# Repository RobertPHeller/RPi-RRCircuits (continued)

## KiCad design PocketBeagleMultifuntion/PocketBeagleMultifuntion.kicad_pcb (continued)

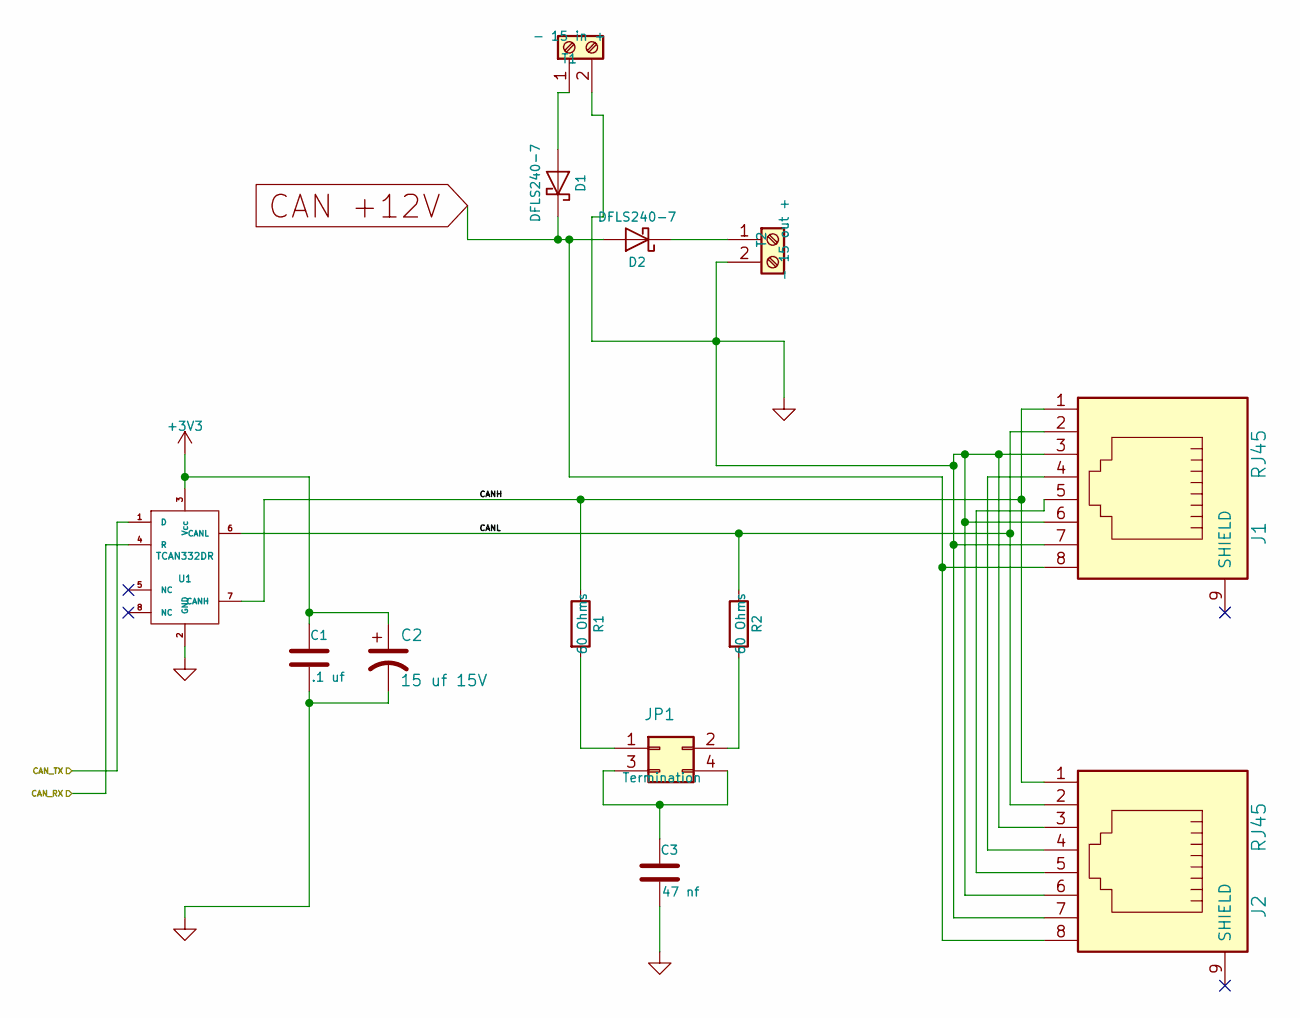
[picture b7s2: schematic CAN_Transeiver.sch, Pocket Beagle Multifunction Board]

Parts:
C1: .1 uf; C_0603; Mouser Part Number 710-885012206095
C2: 15 uf 15V; CP_Elec_4x5.7; Mouser Part Number 647-UUD1C150MCL
C3: 47 nf; C_0603; Mouser Part Number 710-885012206093
D1, D2: DFLS240-7; D_SMB; Mouser Part Number 621-DFLS240-7
J1, J2: RJ45; RJ45_8N-S; Mouser Part Number 710-615008144221
JP1: Termination; Pin_Header_Straight_2x02_Pitch2.54mm; Mouser Part Number 649-67997-404HLF
R1, R2: 60 Ohms; R_1206; Mouser Part Number 71-CRCW120660R0KNAIF
T1: - 15 in +; TerminalBlock_Pheonix_MPT-2.54mm_2pol; Mouser Part Number 651-1725656
T2: - 15 out +; TerminalBlock_Pheonix_MPT-2.54mm_2pol; Mouser Part Number 651-1725656
U1: TCAN332DR; SOIC-8_3.9x4.9mm_Pitch1.27mm; Mouser Part Number 595-TCAN332DR

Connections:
+3V3: C1.1, C2.1, U1.3 (Vcc); also elsewhere on the board
/CAN1_RX: U1.4 (R); also elsewhere on the board
/CAN1_TX: U1.1 (D); also elsewhere on the board
/CAN Transceiver/CANH: J1.1, J2.1, R1.1, U1.7 (CANH)
/CAN Transceiver/CANL: J1.2, J2.2, R2.1, U1.6 (CANL)
CAN +12V: D1.1 (K), D2.2 (A), J1.8, J2.8; also elsewhere on the board
GND: C1.2, C2.2, C3.2, J1.3, J1.6, J1.7, J2.3, J2.6, J2.7, T1.2, T2.2, U1.2 (GND); also elsewhere on the board
unnamed: C3.1, JP1.3, JP1.4
unnamed: D1.2 (A), T1.1
unnamed: D2.1 (K), T2.1
unnamed: J1.4, J2.4
unnamed: J1.5, J2.5
unnamed: JP1.1, R1.2
unnamed: JP1.2, R2.2

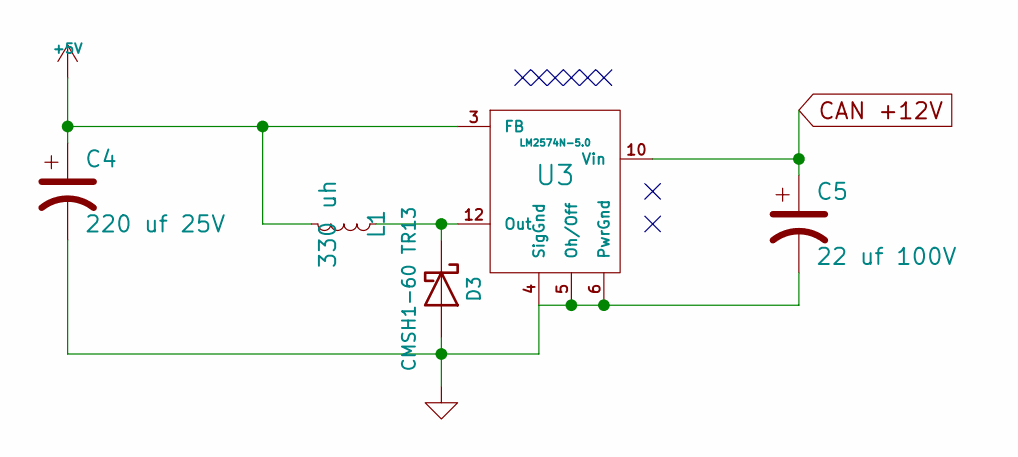
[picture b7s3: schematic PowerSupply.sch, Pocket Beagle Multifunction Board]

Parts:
C4: 220 uf 25V; CP_Elec_8x10; Mouser Part Number 647-UWT1E221MNL1GS
C5: 22 uf 100V; CP_Elec_8x10; Mouser Part Number 647-UUX2A220MNL6GS
D3: CMSH1-60 TR13; D_SMB; Mouser Part Number 610-CMSH1-60TR13
L1: 330 uh; SRN1060; Mouser Part Number 652-SRN1060-331M
U3: LM2574N-5.0; SOIC-14_7.4x8.7mm_Pitch1.27mm; Mouser Part Number 926-LM2574N-5.0/NOPB

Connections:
+5V: C4.1, L1.2, U3.3 (FB); also elsewhere on the board
CAN +12V: C5.1, U3.10 (Vin); also elsewhere on the board
GND: C4.2, C5.2, D3.2 (A), U3.4 (SigGnd), U3.5 (Oh/Off), U3.6 (PwrGnd); also elsewhere on the board
unnamed: D3.1 (K), L1.1, U3.12 (Out)

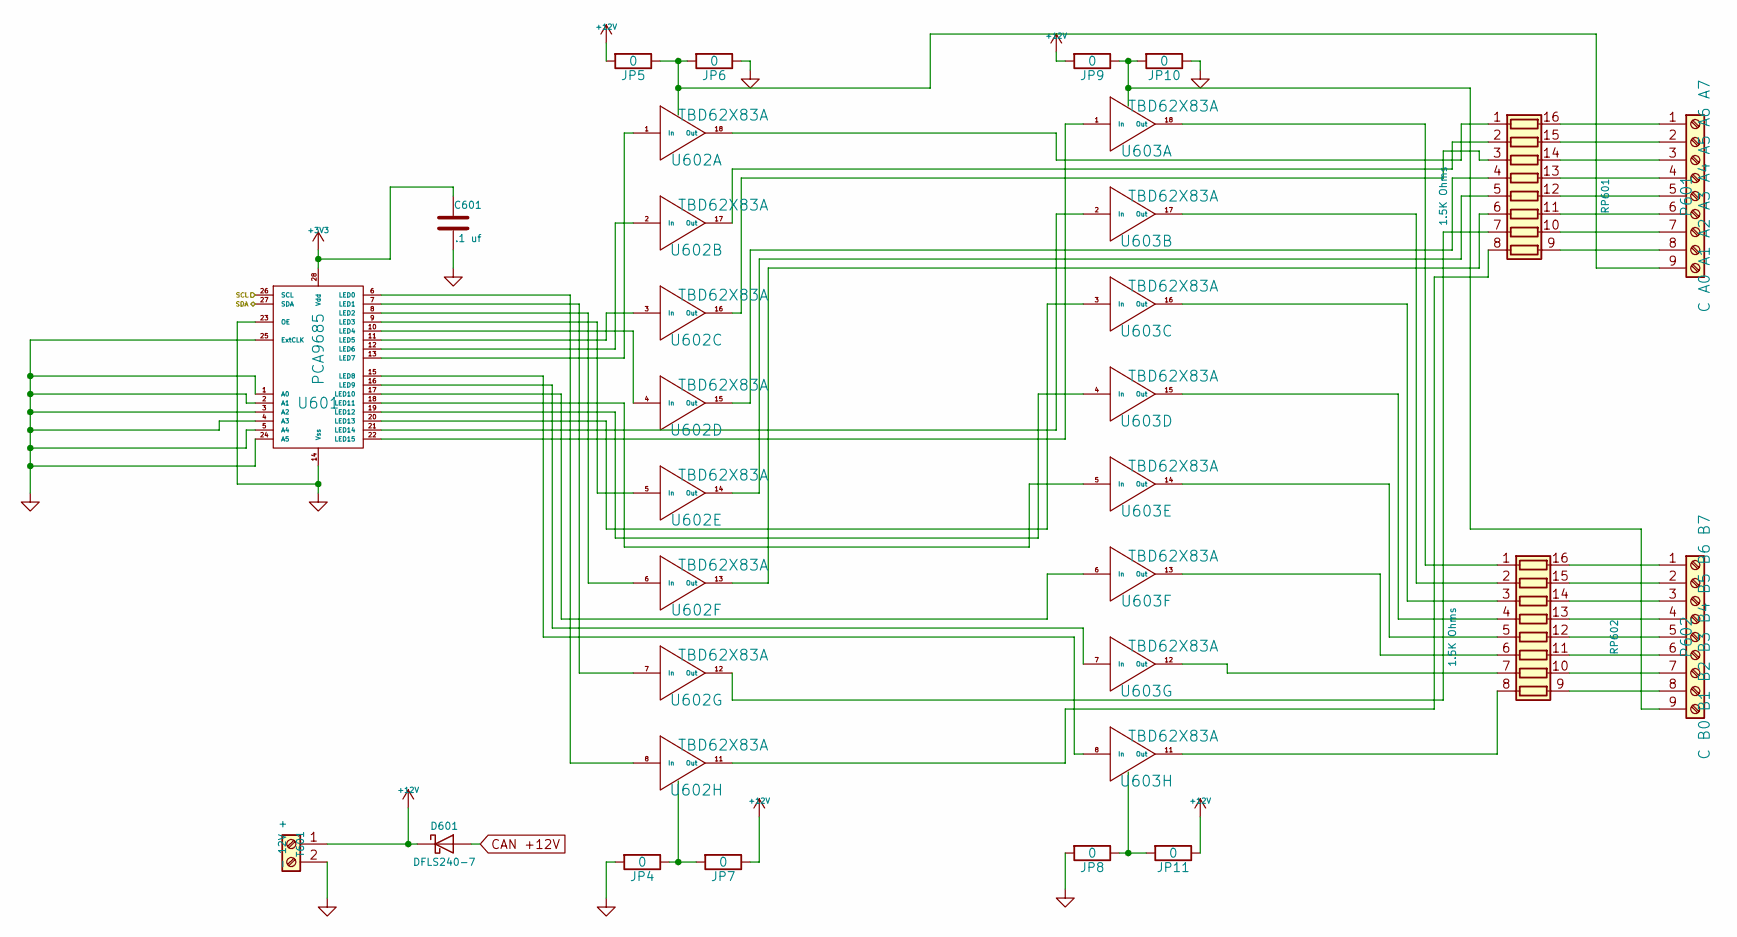
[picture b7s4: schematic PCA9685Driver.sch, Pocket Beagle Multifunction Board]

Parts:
C601: .1 uf; C_0603; Mouser Part Number 710-885012206095
D601: DFLS240-7; D_SMB; Mouser Part Number 621-DFLS240-7
JP4, JP5, JP6, JP7, JP8, JP9, JP10, JP11: 0; R_1206; Mouser Part Number 71-CRCW12060000Z0EBC
P601: C A0 A1 A2 A3 A4 A5 A6 A7; TerminalBlock_Pheonix_MPT-2.54mm_9pol; Mouser Part Number 651-1725724
P602: C B0 B1 B2 B3 B4 B5 B6 B7; TerminalBlock_Pheonix_MPT-2.54mm_9pol; Mouser Part Number 651-1725724
RP601, RP602: 1.5K Ohms; 4816P; Mouser Part Number 652-4816P-T1LF-1.5K
T601: - 12V +; TerminalBlock_Pheonix_MPT-2.54mm_2pol; Mouser Part Number 651-1725656
U601: PCA9685; TSSOP-28_4.4x9.7mm_Pitch0.65mm; Mouser Part Number 771-PCA9685PW,118
U602, U603: TBD62X83A; SOIC-18W_7.5x11.6mm_Pitch1.27mm; Mouser Part Number 757-TBD62083AFG or 757-TBD62783AFG

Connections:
+3V3: C601.1, U601.28 (Vdd); also elsewhere on the board
+12V: D601.1 (K), JP5.2, JP7.1, JP9.2, JP11.1, T601.1; also elsewhere on the board
/SCL: U601.26 (SCL); also elsewhere on the board
/SDA: U601.27 (SDA); also elsewhere on the board
CAN +12V: D601.2 (A); also elsewhere on the board
GND: C601.2, JP4.2, JP6.1, JP8.2, JP10.1, T601.2, U601.1 (A0), U601.2 (A1), U601.3 (A2), U601.4 (A3), U601.5 (A4), U601.14 (Vss), U601.23 (OE), U601.24 (A5), U601.25 (ExtCLK); also elsewhere on the board
unnamed: JP4.1, JP7.2, U602.9 (IC)
unnamed: JP5.1, JP6.2, P601.9, U602.10 (OC)
unnamed: JP9.1, JP10.2, P602.9, U603.10 (OC)
unnamed: JP8.1, JP11.2, U603.9 (IC)
unnamed: P601.1, RP601.16 (R1.2)
unnamed: P601.2, RP601.15 (R2.2)
unnamed: P601.3, RP601.14 (R3.2)
unnamed: P601.4, RP601.13 (R4.2)
unnamed: P601.5, RP601.12 (R5.2)
unnamed: P601.6, RP601.11 (R6.2)
unnamed: P601.7, RP601.10 (R7.2)
unnamed: P601.8, RP601.9 (R8.2)
unnamed: P602.1, RP602.16 (R1.2)
unnamed: P602.2, RP602.15 (R2.2)
unnamed: P602.3, RP602.14 (R3.2)
unnamed: P602.4, RP602.13 (R4.2)
unnamed: P602.5, RP602.12 (R5.2)
unnamed: P602.6, RP602.11 (R6.2)
unnamed: P602.7, RP602.10 (R7.2)
unnamed: P602.8, RP602.9 (R8.2)
unnamed: RP601.1 (R1.1), U602.18 (Out)
unnamed: RP601.2 (R2.1), U602.17 (Out)
unnamed: RP601.3 (R3.1), U602.16 (Out)
unnamed: RP601.4 (R4.1), U602.15 (Out)
unnamed: RP601.5 (R5.1), U602.14 (Out)
unnamed: RP601.6 (R6.1), U602.13 (Out)
unnamed: RP601.7 (R7.1), U602.12 (Out)
unnamed: RP601.8 (R8.1), U602.11 (Out)
unnamed: RP602.1 (R1.1), U603.18 (Out)
unnamed: RP602.2 (R2.1), U603.17 (Out)
unnamed: RP602.3 (R3.1), U603.16 (Out)
unnamed: RP602.4 (R4.1), U603.15 (Out)
unnamed: RP602.5 (R5.1), U603.14 (Out)
unnamed: RP602.6 (R6.1), U603.13 (Out)
unnamed: RP602.7 (R7.1), U603.12 (Out)
unnamed: RP602.8 (R8.1), U603.11 (Out)
unnamed: U601.6 (LED0), U602.8 (In)
unnamed: U601.7 (LED1), U602.7 (In)
unnamed: U601.8 (LED2), U602.6 (In)
unnamed: U601.9 (LED3), U602.5 (In)
unnamed: U601.10 (LED4), U602.4 (In)
unnamed: U601.11 (LED5), U602.3 (In)
unnamed: U601.12 (LED6), U602.2 (In)
unnamed: U601.13 (LED7), U602.1 (In)
unnamed: U601.15 (LED8), U603.8 (In)
unnamed: U601.16 (LED9), U603.7 (In)
unnamed: U601.17 (LED10), U603.6 (In)
unnamed: U601.18 (LED11), U603.5 (In)
unnamed: U601.19 (LED12), U603.4 (In)
unnamed: U601.20 (LED13), U603.3 (In)
unnamed: U601.21 (LED14), U603.2 (In)
unnamed: U601.22 (LED15), U603.1 (In)

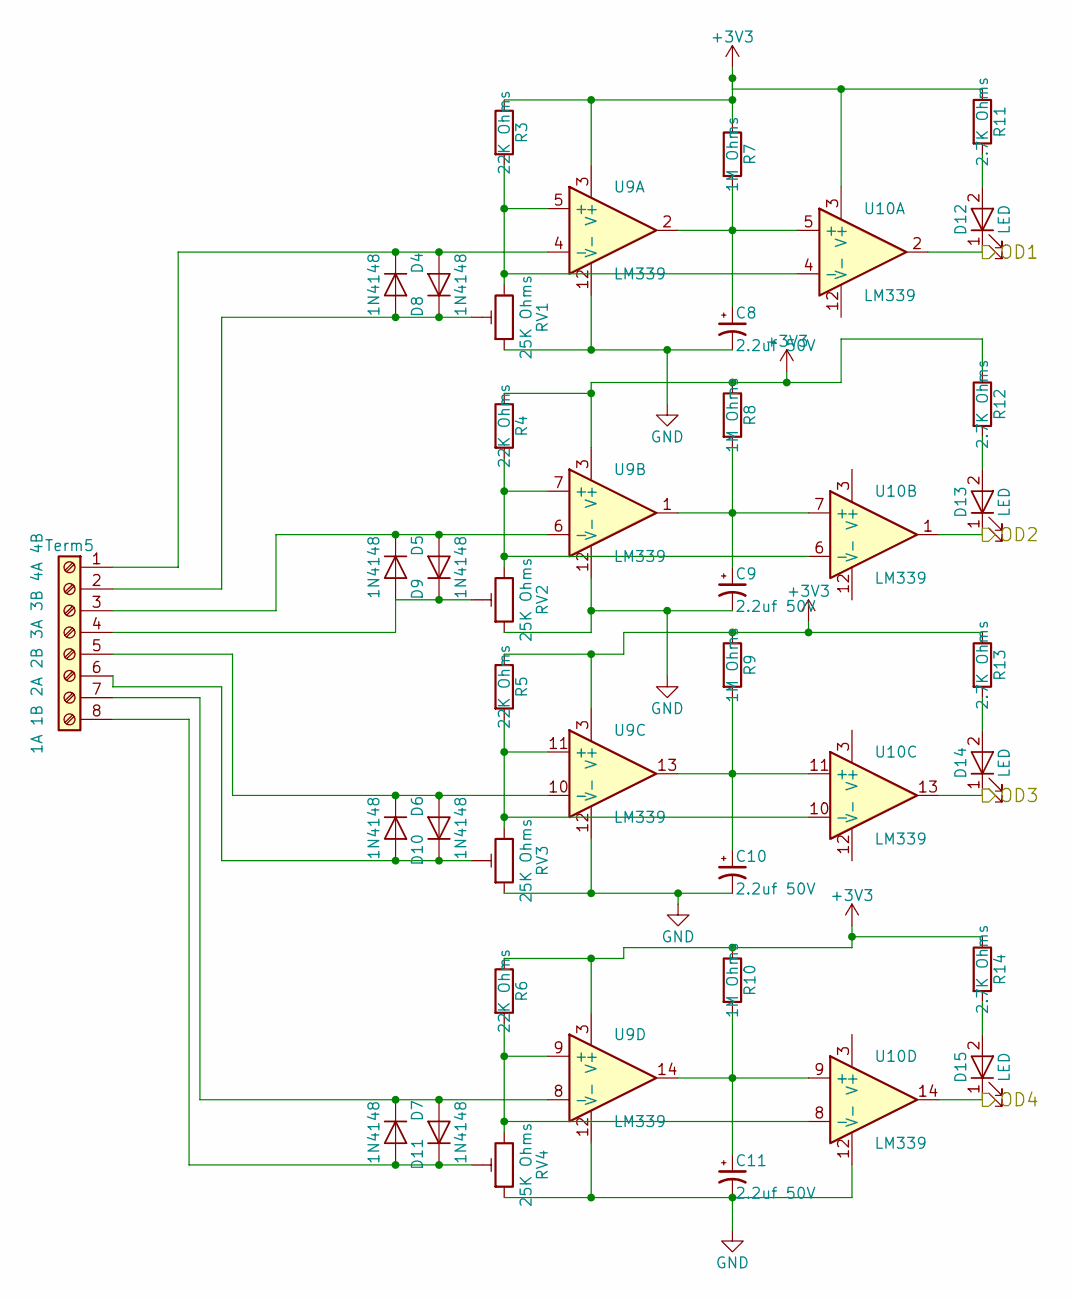
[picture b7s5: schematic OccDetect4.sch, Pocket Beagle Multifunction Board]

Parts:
C8, C9, C10, C11: 2.2uf 50V; CP_Elec_4x5.7; Mouser Part Number 710-865080140002
D4, D5, D6, D7, D8, D9, D10, D11: 1N4148; D_SOD-123; Mouser Part Number 750-1N4148WS-HF
D12, D13, D14, D15: LED; LED_0603; Mouser Part Number 710-150060SS55040
R3, R4, R5, R6: 22K Ohms; R_0603; Mouser Part Number 71-RCG060322K0JNEA
R7, R8, R9, R10: 1M Ohms; R_0603; Mouser Part Number 71-CRCW06031M00JNEAC
R11, R12, R13, R14: 2.7K Ohms; R_0603; Mouser Part Number 71-CRCW06032K70JNEAC
RV1, RV2, RV3, RV4: 25K Ohms; Potentiometer_Trimmer_Bourns_3214J; Mouser Part Number 652-3314J-1-253E
Term5: 1A 1B 2A 2B 3A 3B 4A 4B; TerminalBlock_Pheonix_MPT-2.54mm_8pol; Mouser Part Number 651-1725711
U9, U10: LM339; SOIC-14_3.9x8.7mm_Pitch1.27mm

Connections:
+3V3: R3.1, R4.1, R5.1, R6.1, R7.1, R8.1, R9.1, R10.1, R11.1, R12.1, R13.1, R14.1, U9.3 (V+), U10.3 (V+); also elsewhere on the board
/GPIO7: D12.1 (K), U10.2; also elsewhere on the board
/GPIO19: D13.1 (K), U10.1; also elsewhere on the board
/GPIO20: D14.1 (K), U10.13; also elsewhere on the board
/GPIO23: D15.1 (K), U10.14; also elsewhere on the board
GND: C8.2, C9.2, C10.2, C11.2, RV1.1, RV2.1, RV3.1, RV4.1, U9.12 (V-), U10.12 (V-); also elsewhere on the board
unnamed: C8.1, R7.2, U9.2, U10.5 (+)
unnamed: C9.1, R8.2, U9.1, U10.7 (+)
unnamed: C10.1, R9.2, U9.13, U10.11 (+)
unnamed: C11.1, R10.2, U9.14, U10.9 (+)
unnamed: D4.1 (K), D8.2 (A), Term5.1, U9.4 (-)
unnamed: D4.2 (A), D8.1 (K), RV1.2, Term5.2
unnamed: D5.1 (K), D9.2 (A), Term5.3, U9.6 (-)
unnamed: D5.2 (A), D9.1 (K), RV2.2, Term5.4
unnamed: D6.2 (A), D10.1 (K), RV3.2, Term5.6
unnamed: D6.1 (K), D10.2 (A), Term5.5, U9.10 (-)
unnamed: D7.2 (A), D11.1 (K), RV4.2, Term5.8
unnamed: D7.1 (K), D11.2 (A), Term5.7, U9.8 (-)
unnamed: D12.2 (A), R11.2
unnamed: D13.2 (A), R12.2
unnamed: D14.2 (A), R13.2
unnamed: D15.2 (A), R14.2
unnamed: R3.2, RV1.3, U9.5 (+), U10.4 (-)
unnamed: R4.2, RV2.3, U9.7 (+), U10.6 (-)
unnamed: R5.2, RV3.3, U9.11 (+), U10.10 (-)
unnamed: R6.2, RV4.3, U9.9 (+), U10.8 (-)

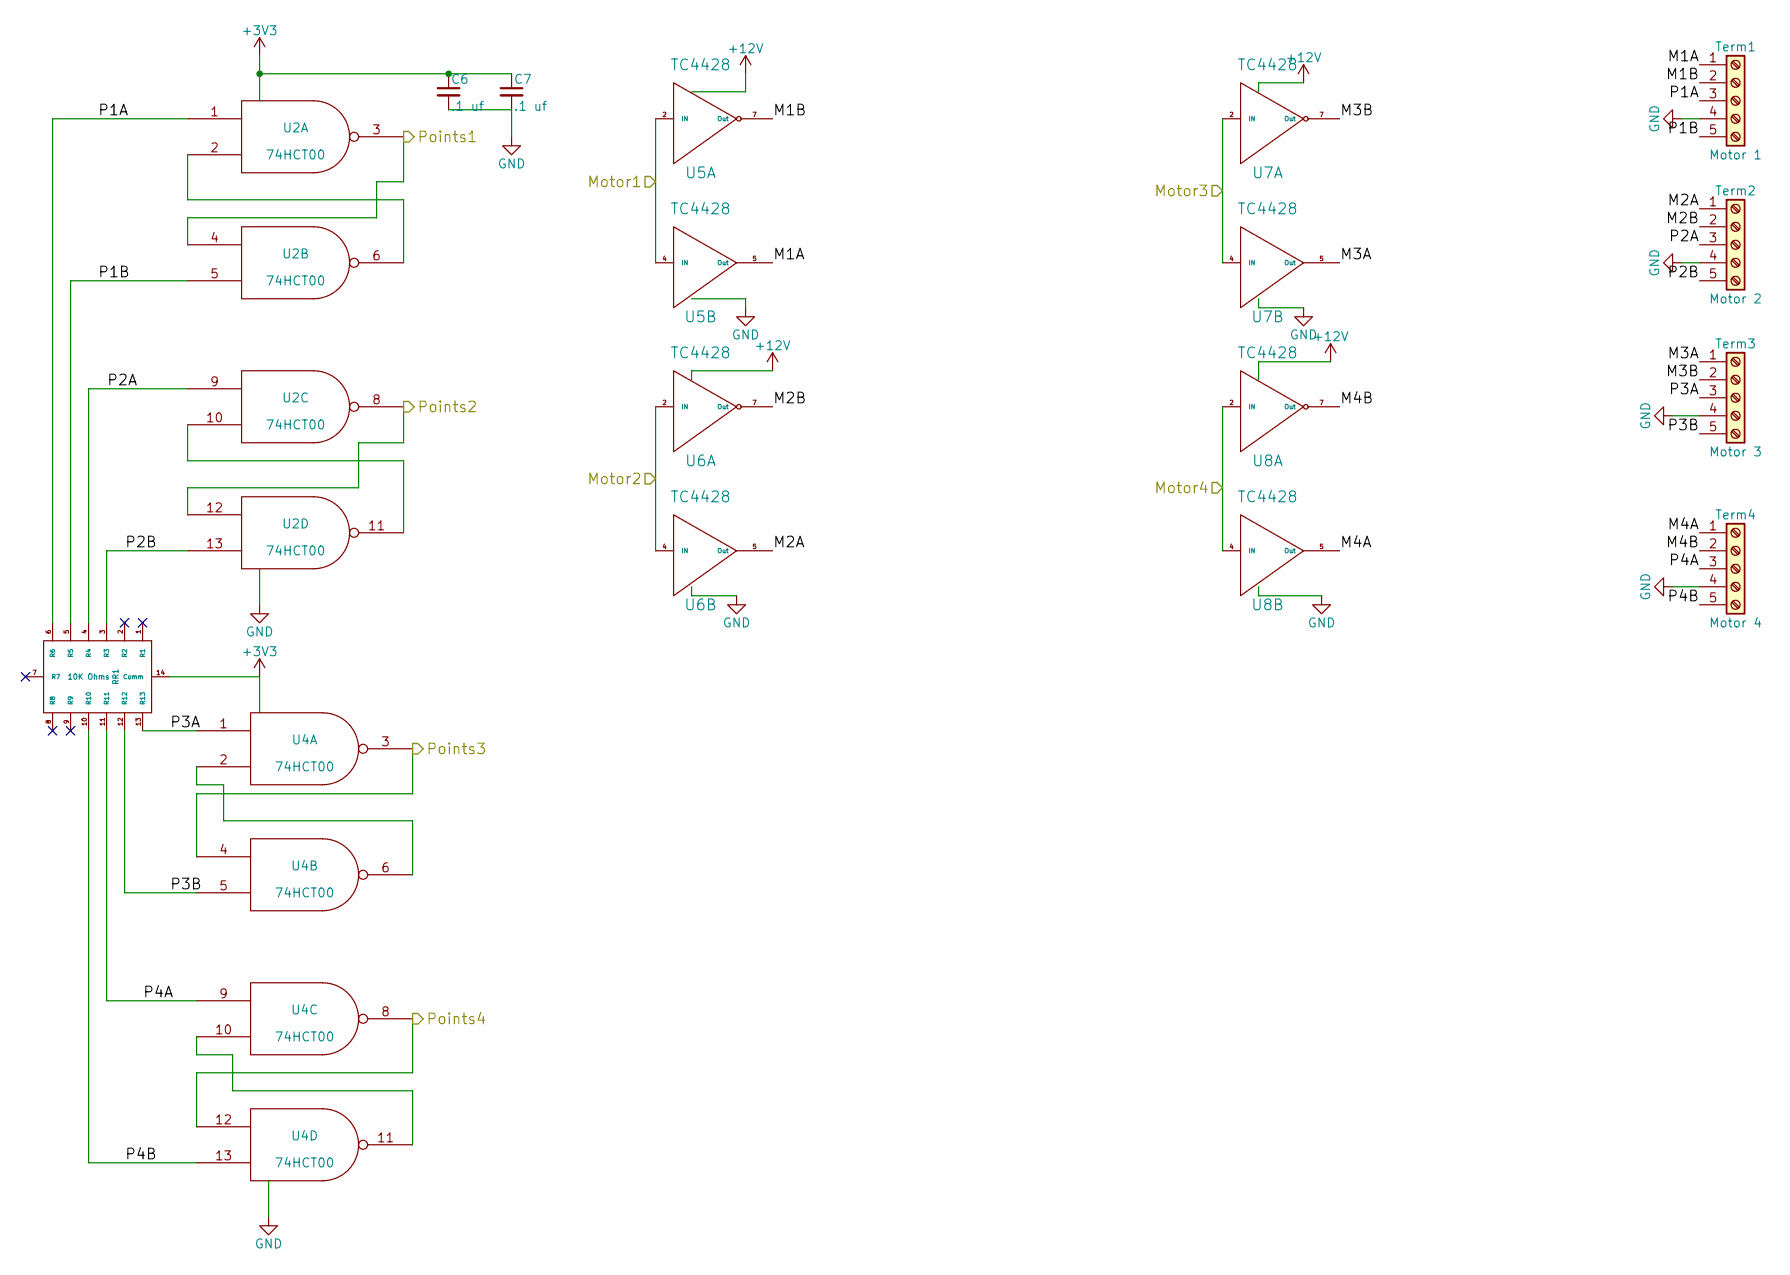
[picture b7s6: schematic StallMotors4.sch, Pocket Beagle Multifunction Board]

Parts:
C6, C7: .1 uf; C_0603; Mouser Part Number 710-885012206095
RR1: 10K Ohms; 4814P; Mouser Part Number 652-4814P-2LF-10K
Term1: Motor 1; TerminalBlock_Pheonix_MPT-2.54mm_5pol; Mouser Part Number 651-1725685
Term2: Motor 2; TerminalBlock_Pheonix_MPT-2.54mm_5pol; Mouser Part Number 651-1725685
Term3: Motor 3; TerminalBlock_Pheonix_MPT-2.54mm_5pol; Mouser Part Number 651-1725685
Term4: Motor 4; TerminalBlock_Pheonix_MPT-2.54mm_5pol; Mouser Part Number 651-1725685
U2: 74HCT00; SOIC-14_3.9x8.7mm_Pitch1.27mm
U4: 74HCT00; SOIC-14_3.9x8.7mm_Pitch1.27mm; Mouser Part Number 595-SN74AHC00D
U5, U6, U7, U8: TC4428; SOIC-8_3.9x4.9mm_Pitch1.27mm; Mouser Part Number 579-TC4428VOA

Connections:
+3V3: C6.1, C7.1, RR1.14 (Comm), U2.14 (VCC), U4.14 (VCC); also elsewhere on the board
+12V: U5.6 (Vdd), U6.6 (Vdd), U7.6 (Vdd), U8.6 (Vdd); also elsewhere on the board
/GPIO26: U5.2 (IN), U5.4 (IN); also elsewhere on the board
/GPIO27: U6.2 (IN), U6.4 (IN); also elsewhere on the board
/GPIO45: U7.2 (IN), U7.4 (IN); also elsewhere on the board
/GPIO46: U8.2 (IN), U8.4 (IN); also elsewhere on the board
/GPIO47: U2.3, U2.4; also elsewhere on the board
/GPIO48: U2.8, U2.12; also elsewhere on the board
/GPIO50: U4.3, U4.4; also elsewhere on the board
/GPIO52: U4.8, U4.12; also elsewhere on the board
/Stall Motors/M1A: Term1.1, U5.5 (Out)
/Stall Motors/M1B: Term1.2, U5.7 (Out)
/Stall Motors/M2A: Term2.1, U6.5 (Out)
/Stall Motors/M2B: Term2.2, U6.7 (Out)
/Stall Motors/M3A: Term3.1, U7.5 (Out)
/Stall Motors/M3B: Term3.2, U7.7 (Out)
/Stall Motors/M4A: Term4.1, U8.5 (Out)
/Stall Motors/M4B: Term4.2, U8.7 (Out)
/Stall Motors/P1A: RR1.6 (R6), Term1.3, U2.1
/Stall Motors/P1B: RR1.5 (R5), Term1.5, U2.5
/Stall Motors/P2A: RR1.4 (R4), Term2.3, U2.9
/Stall Motors/P2B: RR1.3 (R3), Term2.5, U2.13
/Stall Motors/P3A: RR1.13 (R13), Term3.3, U4.1
/Stall Motors/P3B: RR1.12 (R12), Term3.5, U4.5
/Stall Motors/P4A: RR1.11 (R11), Term4.3, U4.9
/Stall Motors/P4B: RR1.10 (R10), Term4.5, U4.13
GND: C6.2, C7.2, Term1.4, Term2.4, Term3.4, Term4.4, U2.7 (GND), U4.7 (GND), U5.3 (GND), U6.3 (GND), U7.3 (GND), U8.3 (GND); also elsewhere on the board
unnamed: U2.2, U2.6
unnamed: U2.10, U2.11
unnamed: U4.2, U4.6
unnamed: U4.10, U4.11

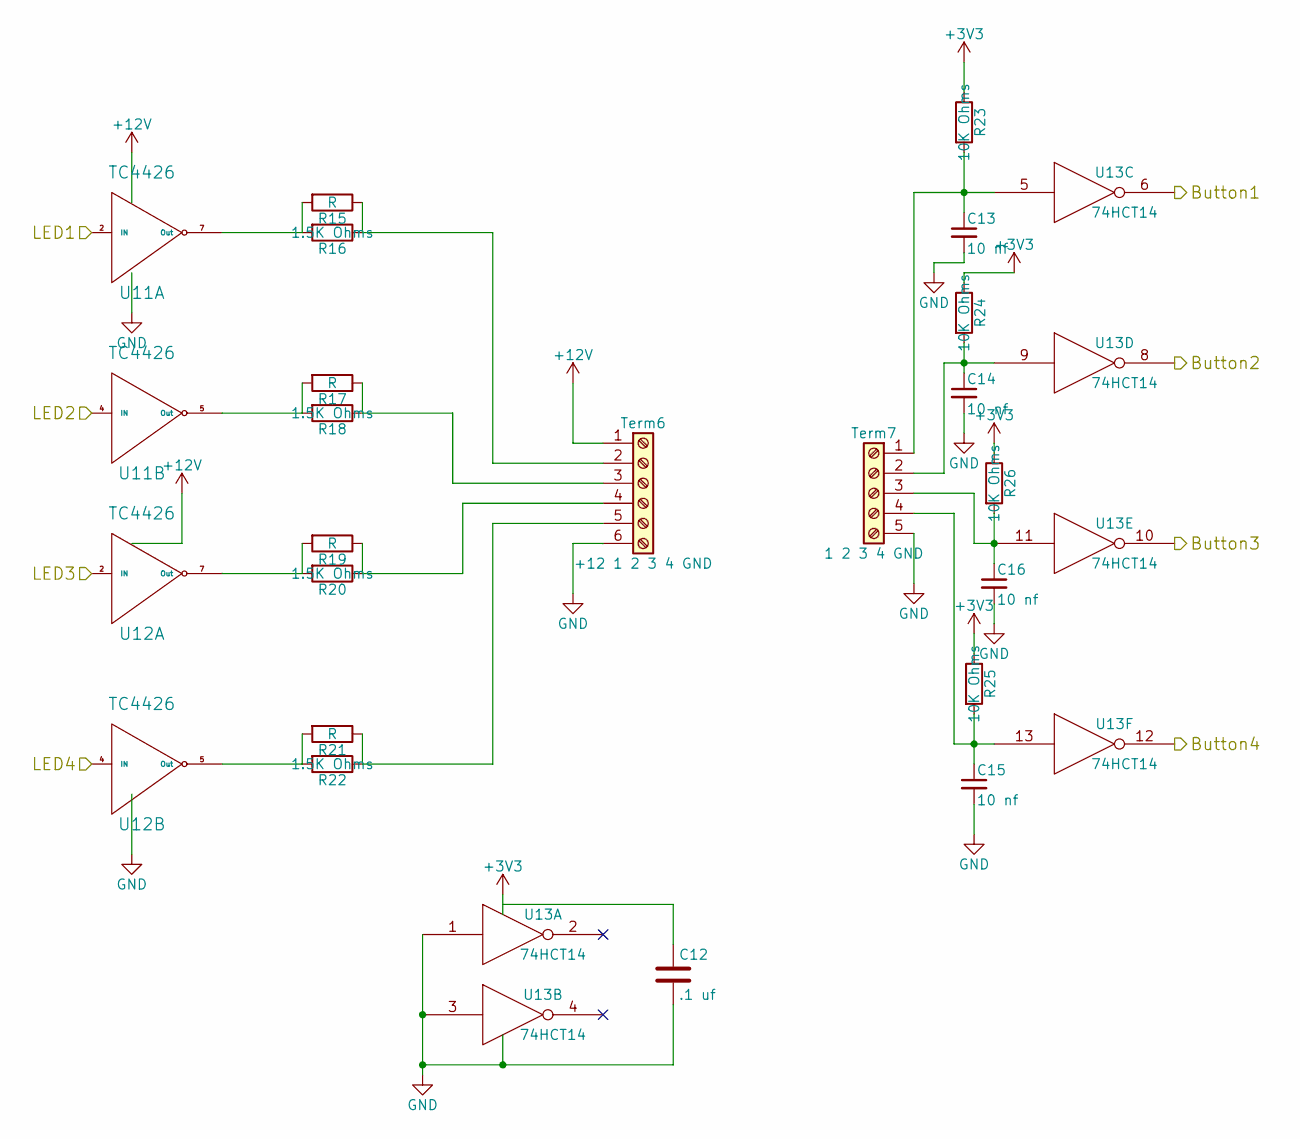
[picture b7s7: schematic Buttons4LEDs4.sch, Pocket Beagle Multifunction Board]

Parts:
C12: .1 uf; C_0603
C13, C14, C15, C16: 10 nf; C_0603; Mouser Part Number 710-885382206002
R15, R17, R19, R21: R; R_Axial_DIN0207_L6.3mm_D2.5mm_P7.62mm_Horizontal
R16, R18, R20, R22: 1.5K Ohms; R_0603; Mouser Part Number 71-CRCW06031K50JNEAC
R23, R24, R25, R26: 10K Ohms; R_0603; Mouser Part Number 71-CRCW060310K0JNEBC
Term6: +12 1 2 3 4 GND; TerminalBlock_Pheonix_MPT-2.54mm_6pol; Mouser Part Number 651-1725698
Term7: 1 2 3 4 GND; TerminalBlock_Pheonix_MPT-2.54mm_5pol; Mouser Part Number 651-1725685
U11, U12: TC4426; SOIC-8_3.9x4.9mm_Pitch1.27mm
U13: 74HCT14; SOIC-14_3.9x8.7mm_Pitch1.27mm; Mouser Part Number 595-CD74HC14M

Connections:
+3V3: R23.1, R24.1, R25.1, R26.1, U13.14 (VCC); also elsewhere on the board
/GPIO57: U13.6; also elsewhere on the board
/GPIO58: U13.8; also elsewhere on the board
/GPIO59: U13.10; also elsewhere on the board
/GPIO60: U13.12; also elsewhere on the board
/GPIO64: U11.2 (IN); also elsewhere on the board
/GPIO65: U11.4 (IN); also elsewhere on the board
/GPIO86: U12.2 (IN); also elsewhere on the board
/GPIO87: U12.4 (IN); also elsewhere on the board
GND: C12.2, C13.2, C14.2, C15.2, C16.2, Term6.6, Term7.5, U11.3 (GND), U12.3 (GND), U13.1, U13.3, U13.7 (GND); also elsewhere on the board
unnamed: C13.1, R23.2, Term7.1, U13.5
unnamed: C14.1, R24.2, Term7.2, U13.9
unnamed: C15.1, R25.2, Term7.4, U13.13
unnamed: C16.1, R26.2, Term7.3, U13.11
unnamed: R15.1, R16.1, Term6.2
unnamed: R15.2, R16.2, U11.7 (Out)
unnamed: R17.1, R18.1, Term6.3
unnamed: R17.2, R18.2, U11.5 (Out)
unnamed: R19.1, R20.1, Term6.4
unnamed: R19.2, R20.2, U12.7 (Out)
unnamed: R21.1, R22.1, Term6.5
unnamed: R21.2, R22.2, U12.5 (Out)
V+: Term6.1, U11.6 (Vdd), U12.6 (Vdd)

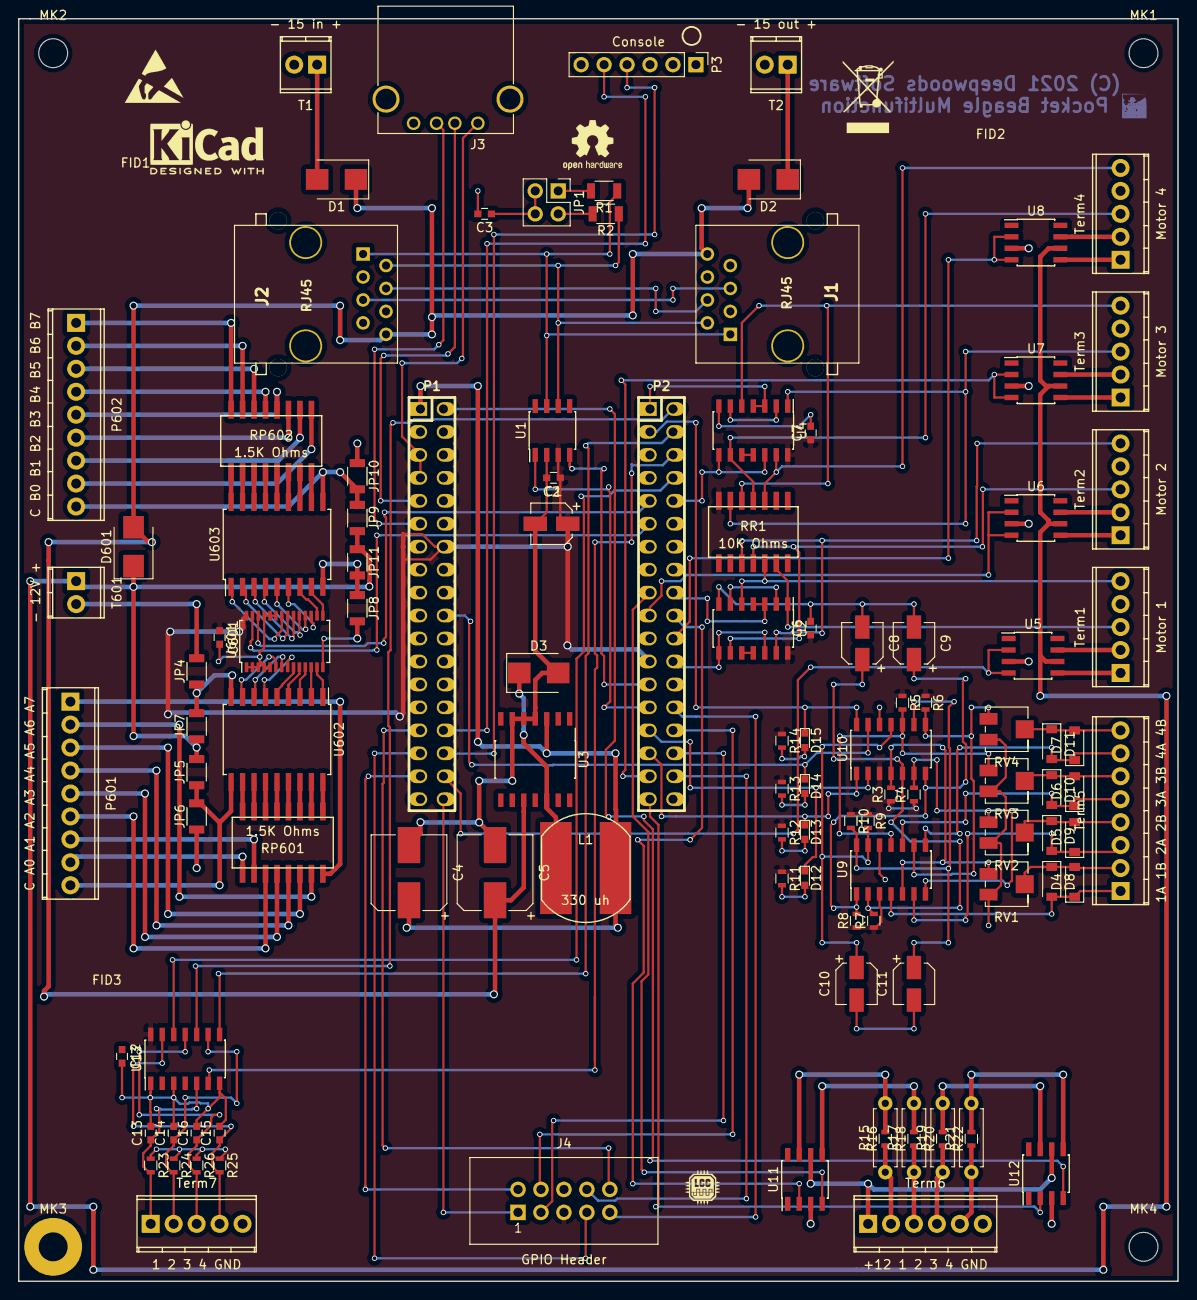
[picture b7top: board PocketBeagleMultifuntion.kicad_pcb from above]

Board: 2 copper layers, 128.3 x 139.7 mm, 118 parts (0 on the bottom side), 157 nets.
